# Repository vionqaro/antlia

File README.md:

View this project on [CADLAB.io](https://cadlab.io/project/30606). 

# antlia

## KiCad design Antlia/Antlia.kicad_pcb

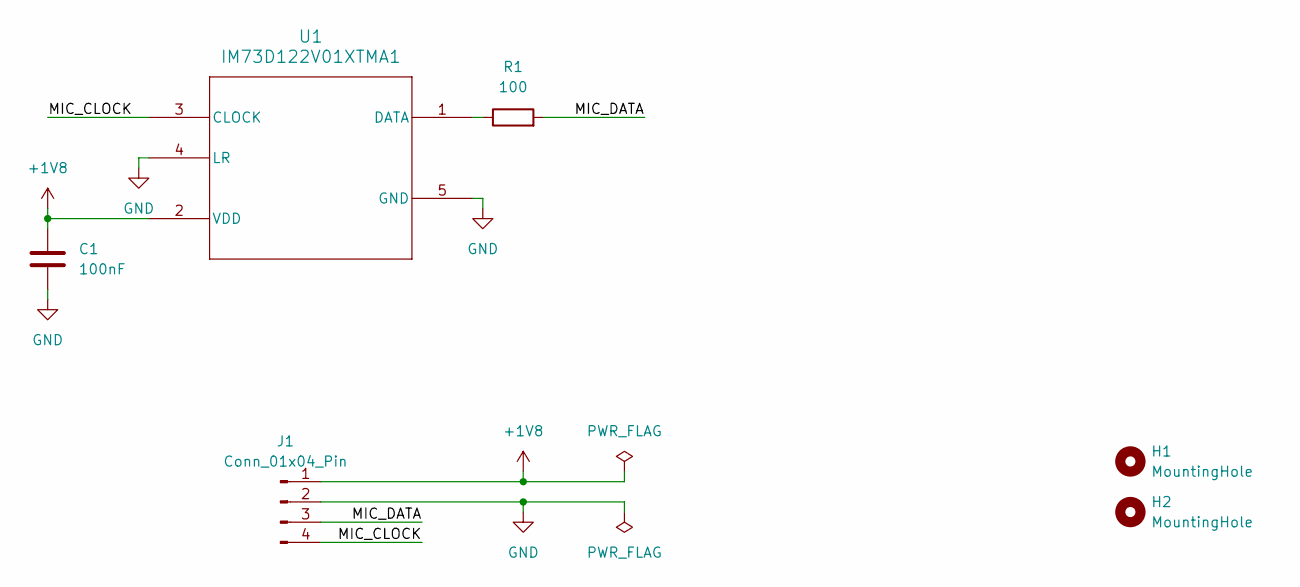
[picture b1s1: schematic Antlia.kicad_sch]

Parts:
C1: 100nF; C_0603_1608Metric
H1, H2: MountingHole; MountingHole_2.2mm_M2
J1: Conn_01x04_Pin; PinHeader_1x04_P2.54mm_Vertical
R1: 100; C_0603_1608Metric
U1: IM73D122V01XTMA1; Infineon_PG-LLGA-5-2

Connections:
+1V8: C1.1, J1.1, U1.2 (VDD)
/MIC_CLOCK: J1.4, U1.3 (CLOCK)
/MIC_DATA: J1.3, R1.2
GND: C1.2, J1.2, U1.4 (LR), U1.5 (GND)
unnamed: R1.1, U1.1 (DATA)

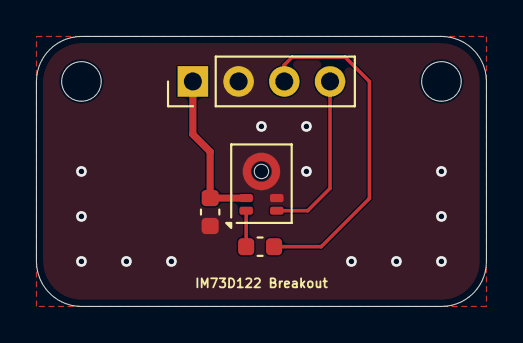
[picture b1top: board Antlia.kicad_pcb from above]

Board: 2 copper layers, 25.0 x 15.0 mm, 6 parts (0 on the bottom side), 5 nets.
